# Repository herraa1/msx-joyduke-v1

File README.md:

# Microsoft Xbox Original controller adapter for MSX (msx-joyduke) v1

Connect [Microsoft Xbox Original controllers](https://en.wikipedia.org/wiki/Xbox_controller) to [MSX computers](https://www.msx.org/wiki/).

> [!NOTE]
>
> No build instructions are yet provided, but if you are brave enough go for the [recommended build](#recommended-build).
>

## Introduction

The msx-joyduke v1 is an adapter that allows connecting Microsoft Xbox Original controllers to [MSX general purpose I/O ports](https://www.msx.org/wiki/General_Purpose_port).

The main features of the msx-joyduke v1 adapter are:
* made of widely available electronic components
* behaves as a cord extension between the MSX computer and the Microsoft Xbox Original controller
* uses a female standard DE9 connector on the adapter's MSX joystick side
* uses a Xbox Controller socket on the adapter's Microsoft Xbox Original controller side
* formally requires an external USB power supply as the adapter draws slightly more current than a MSX general purpose I/O interface can officially provide
* optionally, can be powered using a MSX general purpose I/O interface without an external power supply if your MSX can safely supply enough current
* power consumption of ~20mA for the adapter itself, between ~55mA and ~85mA depending on the Xbox controller connected
* serial debug provides information about the operation of the adapter

## [Hardware](hardware/kicad/)

The msx-joyduke v1 adapter uses an [Atmega328p](https://en.wikipedia.org/wiki/ATmega328) and a [MAX3421](https://www.analog.com/media/en/technical-documentation/data-sheets/max3421e.pdf) to convert the [Microsoft Xbox Original controller USB signalling](https://xboxdevwiki.net/Xbox_Input_Devices#USB_Adapters) to the [MSX joystick standard signalling](https://www.msx.org/wiki/Joystick_control).

A two-sided printed circuit board (PCB) is used to put together all components:
* An Atmega328p as the main MCU working at +3.3V and clocked at 8MHz
* A MAX3421 USB Host Controller with SPI interface
* A TPS2051C 500mA current limited switch for the host controller USB port
* An AMS1117-3.3 regulator to convert the 5V from the joystick or the mini USB port to the 3.3V used by the Atmega328p and the MAX3421 chips
* Two 74LS03 quad 2-input NAND gates with open collectors to completely mimic the standard MSX joystick behavior
* A PTC fuse to minimize damage to the MSX computer in case something goes wrong with the board
* Several additional required components (crystals/resonators, diodes, leds, resistors, ceramic capacitors and alumionium capacitors)
* A 9pin PH2.0 connector is used to connect the MSX cable extension
* A 5pin PH2.0 connector is used to connect the Xbox cable extension
* A 2.54 pitch debug header is added for serial debug and programming
* An ICSP header is provided for burning a bootloader or to flash the chip using a hardware programmer

Connection to the MSX general purpose I/O port is implemented using a DE9 joystick extension cable with a female DE9 connector on one side and a loose end on the other side.
The MSX joystick extension cable loose end is wired according to the following pinout mapping.

|  |
|:--|
| MSX joystick connector pinout, from controller plug side |

| MSX side pin | Cable color (may vary) | Signal |
| ------------ | ---------------------- | ------ |
| 5            | Brown                  | +5v    |
| 4            | Orange                 | RIGHT  |
| 3            | Grey                   | LEFT   |
| 2            | Black                  | DOWN   |
| 1            | Red                    | UP     |
| 6            | Green                  | TRIGA  |
| 7            | White                  | TRIGB  |
| 8            | Blue                   | OUT    |
| 9            | Yellow                 | GND    |

The msx-joyduke-v1 is fully compatible with MSX joysticks and honors the pin8 (OUT) signal.

Connection to the Microsoft Xbox Original controller is done via a PC USB for Microsoft Xbox Original controller converter adapter cable with a male socket (the ones present on the Xbox console itself).

|  |
|:--|
| PC USB for Microsoft Xbox Original controller adapter cable |

The cable is severed to get rid of the USB side (which can be used for other projects) exposing the USB wiring.

|  |
|:--|
| Microsoft Xbox Original connector pinout, from Microsoft Xbox Original controller side |

| Cable color official | Signal       | Comment                                                                   |
| ---------------------| ------------ | ------------------------------------------------------------------------- |
| Green                | D+           | USB Data +                                                                |
| White                | D-           | USB Data -                                                                |
| Yellow               | VSync        | (not used)                                                                |
| Black                | GND          | ground                                                                    |
| Red                  | +5V          | +5V power                                                                 |

The Microsoft Xbox Original controller uses 5V for power and logic.

### Recommended Build

Please, use [msx-joyduke-v1 Build2](#build2) for making new boards.

### [Build2](hardware/kicad/msx-joyduke-v1-build2)

[Bill Of Materials (BoM)](https://html-preview.github.io/?url=https://raw.githubusercontent.com/herraa1/msx-joyduke-v1/main/hardware/kicad/msx-joyduke-v1-build2/bom/ibom.html)

This is the first publicly released build of the msx-joyduke adapter.

## [Firmware](firmware/msx-joyduke-v1/)

The msx-joyduke v1 adapter firmware uses the [USB Host Shield 2.0 library](https://github.com/felis/USB_Host_Shield_2.0) to read the Microsoft Xbox Original controller status.

While developing the firmware, I noticed that some Xbox Original controllers were not working as expected. After a bit of troubleshooting the root cause was found and a [modification](https://github.com/felis/USB_Host_Shield_2.0/commit/b92fa02546dddd2278cd411e5d0e2d2ff614c8d8) to the library has been submitted and merged to fix the problem.

The following elements are used as inputs:
* digital pad (D-Pad), as direction arrows
* left and right analog pad as direction arrows
* A button, as Trigger 1
* B button, as Trigger 2

Those elements' status are processed by the msx-joyduke firmware and transformed into MSX general purpose I/O port's signals on the fly.

## [Enclosure](enclosure/)

### Acrylic

A simple acrylic enclosure design for the project is provided to protect the electronic components and provide strain relief for the extension cords.

The enclosure uses a 3mm acrylic sheet.

## Powering the msx-joyduke adapter

The msx-joyduke adapter uses under ~20mA when operating without a controller connected, but the power consumption can rise to ~85mA when an Xbox controller is connected.

On the other hand, a single MSX general purpose I/O interface is capable of delivering up to 50mA according to the MSX standard [^1].

That means that we are slightly over the max current specification for the MSX general purpose I/O interface.

Thus, the safest way to power the msx-joyduke adapter is by powering it via the USB mini connector of the board using an external 5V USB power supply. The board automatically powers up when using the USB mini connector without enabling any switch.

Nevertheless, even if the MSX especification puts such a low limit on the current that can be drawn from a general purpose I/O interface, real MSX hardware usually can safely deliver enough current for the msx-joyduke adapter to work correctly without harming our beloved classic computers.

Taking that into account, the msx-joyduke adapter has been enabled to be optionally powered by the a MSX general purpose I/O interface port.

To enable powering the msx-joyduke adapter from the _MSX Joystick Port_, the switch SW1 _JOYPWR_ must be first turned on by sliding the switch handle to the left.

> [!NOTE]
> A [1N5819 SMD Schottky diode](https://www.diodes.com/assets/Datasheets/1N5819HW.pdf) D4 is used to avoid leaking current from the msx-joyduke adapter to the MSX in case the msx-joyduke adapter is powered by USB while the _JOYPWR_ switch is ON.
> Another [1N5819 SMD Schottky diode](https://www.diodes.com/assets/Datasheets/1N5819HW.pdf) D3 prevents backpowering the USB side from the MSX side.
> And a Positive Temperature Coeficient (PTC) resettable fuse F1 of 50mA protects the MSX general purpose I/O interface port from excess of current in case something goes horribly wrong on the msx-joyduke adapter side.

To power the msx-joyduke adapter using a MSX general purpose I/O interface we must first understand how the PTC protections on the msx-joyduke adapter are implemented.

The selected PTC is rated for 50mA which is the so called Hold Current (the maximum current that can flow in normal operation). There is also the Trip Current (the minimum current necessary for the PTC to move to high-resistance state) which for the selected PTCs is around 100mA. Those thresholds are dependent on temperature and voltage. And to make things more undeterministic, the behavior of the PTC when current is between those thresholds is undefined (it may trip or not).

In normal operation and for a room temperature of around 25 degrees Celsius, the selected PTCs in practice never trip below 75mA.

> [!NOTE]
> Depending on the exact PTCs installed, the trip current may be slightly different and the adapter may trip at a different point. Unless you buy the PTCs from a reliable source, it is very difficult to know the exact PTC specifications. 
>
> Remember that the PTCs are provided as a safeguard in case something goes really wrong on the adapter, not to act as an exact current limiter to strictly comply with the 50mA per-port MSX specification.

A jumper JP1 can be used to bypass the PTC protections for the _MSX Joystick Port_.

> [!WARNING]
> Bypassing the PTC protection may damage your MSX computer.
> Do not bypass the PTC protections unless you known what you are doing.

By closing JP1 and **if our MSX computer can safely provide more than 85mA on a single MSX general purpose I/O interface**, we can connect the _MSX Joystick Port_ to the MSX computer and turn on the SW1 _JOYPWR_ switch to power the msx-joyduke adapter using a single joystick port.

In summary, we can use the following options to power the msx-joyduke adapter (from safest to less safe):
* via the board USB mini conector
  * turn off the SW1 _JOYPWR_ switch
  * connect a 5V USB power supply to the board USB mini connector
* via one of the MSX general purpose I/O interface, if your MSX can safely provide more than 85mA on each MSX general purpose I/O interface
  * close jumper JP1
  * turn on the SW1 _JOYPWR_ switch
  * connect the _MSX Joystick Port_ to a MSX general purpose I/O interface

## Switches and Buttons

| **Switch** | **State**      | **Description**                                                          |
|------------|----------------|--------------------------------------------------------------------------|
| _JOYPWR_   | Off            | power from MSX computer via a joystick port is off (except logic gates)  |
| _JOYPWR_   | On             | board electronics get power from MSX computer via a joystick port        |

> [!NOTE]
> If you plug a +5V USB power supply to the USB mini connector, the adapter will turn on unconditionally irrespective of the _JOYPWR_ switch position.
>

| **Button**   | **Description**                                                                             |
|--------------|---------------------------------------------------------------------------------------------|
| RESET        | restart the firmware                                                                        |

## LED indicators

| **LED**   | **State**      | **Indication** |
|-----------|----------------|---------------|
| _POWER_   | Off            | board is not receiving 3V3 power |
| _POWER_   | Solid Red      | board is receiving 3V3 power     |
| _JoyPort_ | Off            | no Xbox controller connected or recognized |
| _JoyPort_ | Solid Green    | Xbox controller connected and ready to use |
| _Fault_   | Off            | no power fault detected |
| _Fault_   | Solid Yellow   | excess of current detected on the Xbox connector |

## Compatibility Tests

| **Controller**                        | **Compatible** |
|---------------------------------------|----------------|
| 045e:0202 Microsoft X-Box pad v1 (US) | YES            |
| 045e:0289 Microsoft X-Box pad v2 (US) | YES            |

Other Xbox controllers may work but have not been tested.

## References

MSX general purpose I/O port
* https://www.msx.org/wiki/General_Purpose_port

Xbox controller pinout and protocol
* https://chris-donnelly.github.io/xboxpad.html

Atmega328p pinout
- https://camo.githubusercontent.com/18796d8b7673e3b6c14b6bdfb61d86b58c6f0d670398973abd4207afce960277/68747470733a2f2f692e696d6775722e636f6d2f6e6177657145362e6a7067

USB Host Shield 2.0 Library
* https://github.com/felis/USB_Host_Shield_2.0

[^1]: https://www.msx.org/wiki/General_Purpose_port

## Image Sources

* https://www.oshwa.org/open-source-hardware-logo/
* https://en.wikipedia.org/wiki/File:Numbered_DE9_Diagram.svg

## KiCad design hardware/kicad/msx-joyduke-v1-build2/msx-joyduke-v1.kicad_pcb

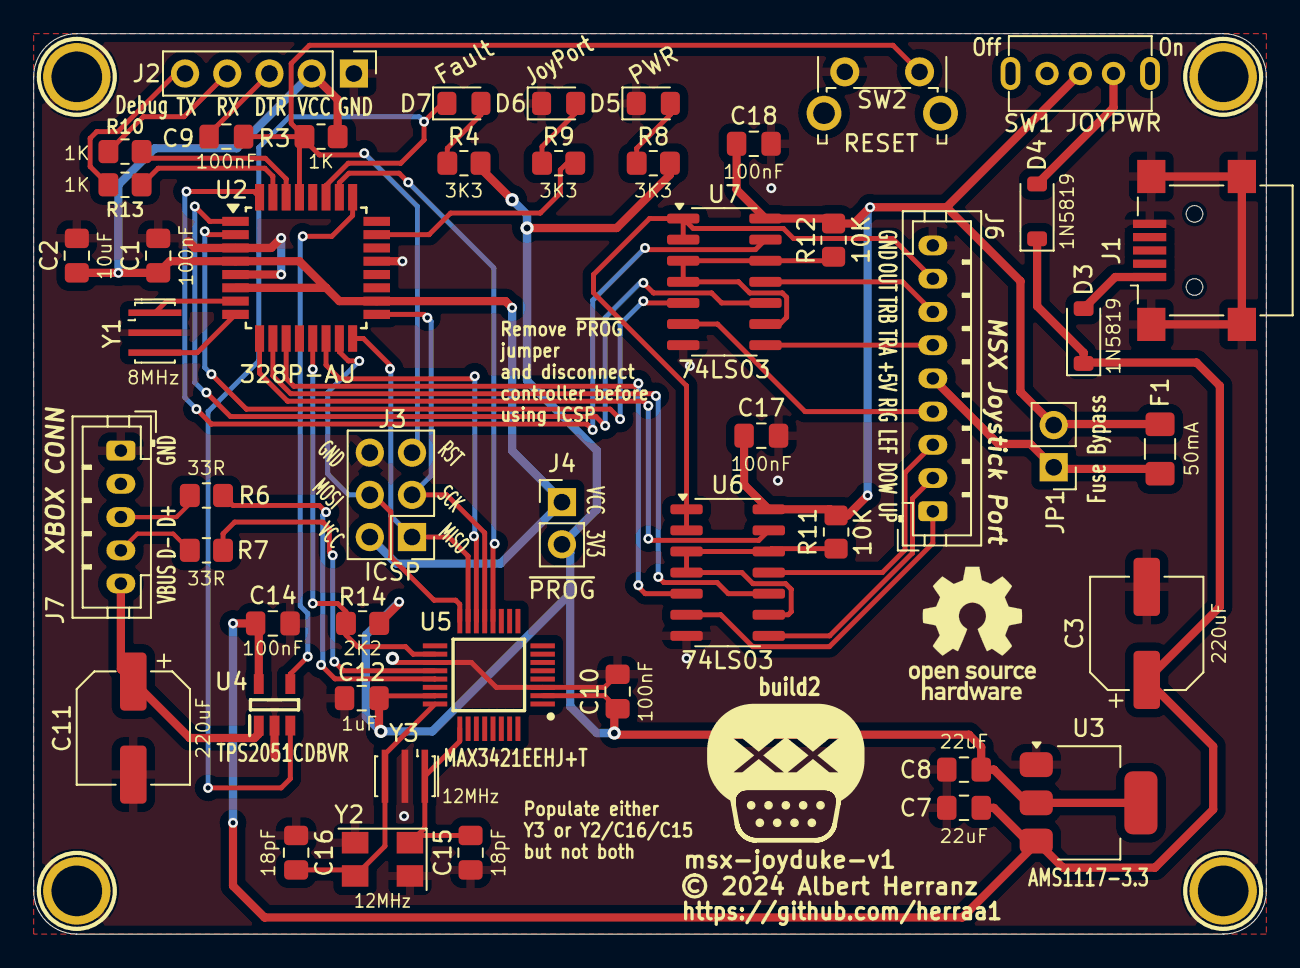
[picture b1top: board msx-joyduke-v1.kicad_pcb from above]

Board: 2 copper layers, 74.2 x 54.2 mm, 54 parts (0 on the bottom side), 50 nets.

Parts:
C1, C9, C10, C14, C17, C18: 100nF; C_0805_2012Metric_Pad1.18x1.45mm_HandSolder
C2: 10uF; C_0805_2012Metric_Pad1.18x1.45mm_HandSolder
C3, C11: 220uF; CP_Elec_6.3x5.4
C7, C8: 22uF; C_0805_2012Metric_Pad1.18x1.45mm_HandSolder
C12: 1uF; C_0805_2012Metric_Pad1.18x1.45mm_HandSolder
C15, C16: 18pF; C_0805_2012Metric_Pad1.18x1.45mm_HandSolder
D3, D4: 1N5819; D_SOD-123
D5: PWR; LED_0805_2012Metric_Pad1.15x1.40mm_HandSolder
D6: JoyPort; LED_0805_2012Metric_Pad1.15x1.40mm_HandSolder
D7: Fault; LED_0805_2012Metric_Pad1.15x1.40mm_HandSolder
F1: 50mA; Fuse_1206_3216Metric_Pad1.42x1.75mm_HandSolder
HOLE1, HOLE2, HOLE3, HOLE4: HOLE; Hole_3mm
J1: USB_B_Mini; USB_Mini-B_Lumberg_2486_01_Horizontal
J2: Debug; PinHeader_1x05_P2.54mm_Vertical
J3: ICSP; PinHeader_2x03_P2.54mm_Vertical
J4: ~{PROG}; PinHeader_1x02_P2.54mm_Vertical
J6: MSX Joystick Port; JST_PH_B9B-PH-K_1x09_P2.00mm_Vertical
J7: XBOX CONN; JST_PH_B5B-PH-K_1x05_P2.00mm_Vertical
JP1: Fuse Bypass; PinHeader_1x02_P2.54mm_Vertical
R3, R10, R13: 1K; R_0805_2012Metric_Pad1.20x1.40mm_HandSolder
R4, R8, R9: 3K3; R_0805_2012Metric_Pad1.20x1.40mm_HandSolder
R6, R7: 33R; R_0805_2012Metric_Pad1.20x1.40mm_HandSolder
R11, R12: 10K; R_0805_2012Metric_Pad1.20x1.40mm_HandSolder
R14: 2K2; R_0805_2012Metric_Pad1.20x1.40mm_HandSolder
SW1: JOYPWR; SW_SK-12D07G6-1P2T-6mm
SW2: RESET; SW_Tactile_SPST_Angled_PTS645Vx39-2LFS
SYM1: Logo_Open_Hardware_Large; OSHW-Logo_7.5x8mm_SilkScreen
U2: 328P-AU; TQFP-32_7x7mm_P0.8mm
U3: AMS1117-3.3; SOT-223-3_TabPin2
U4: TPS2051CDBVR; SOT95P280X145-5N
U5: MAX3421EEHJ+T; QFP50P700X700X120-32N
U6, U7: 74LS03; SOIC-14_3.9x8.7mm_P1.27mm
Y1: 8MHz; Resonator_SMD_Murata_CSTxExxV-3Pin_3.0x1.1mm_HandSoldering
Y2: 12MHz; Crystal_SMD_5032-4Pin_5.0x3.2mm
Y3: 12MHz; Resonator_SMD_Murata_CSTxExxV-3Pin_3.0x1.1mm_HandSoldering

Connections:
+3V3_REG: C8.1, C10.1, C12.1, J4.2, R4.2, R8.2, R14.1, U3.2 (VO), U5.2 (VL), U5.23 (VCC)
+5V_FILT: C3.1, C7.1, C14.1, D3.1 (K), D4.1 (K), U3.3 (VI), U4.5 (IN)
/+3V3_LED: D5.2 (A), R8.1
/D0/RX: R10.1, U2.30 (PD0)
/D1/TX: R13.1, U2.31 (PD1)
/DTR: C9.2, J2.3
/D_N: J7.4, R7.2
/D_P: J7.3, R6.2
/GPIO_J1_DOWN: U2.10 (PD6), U6.10
/GPIO_J1_LEFT: U2.9 (PD5), U6.13
/GPIO_J1_RIGHT: U2.2 (PD4), U7.5
/GPIO_J1_TRIGA: U2.1 (PD3), U7.10
/GPIO_J1_TRIGB: U2.32 (PD2), U7.13
/GPIO_J1_UP: U2.11 (PD7), U6.5
/J1_DOWN: J6.2, U6.8
/J1_LEFT: J6.3, U6.11
/J1_OUT: J6.8, U6.1, U6.2, U7.1, U7.2
/J1_RIGHT: J6.4, U7.6
/J1_TRIGA: J6.6, U7.8
/J1_TRIGB: J6.7, U7.11
/J1_UP: J6.1, U6.6
/JOY_EXT_5V: D4.2 (A), SW1.1 (A)
/MISO: J3.1, U2.16 (PB4), U5.15 (MISO)
/MOSI: J3.4, U2.15 (PB3), U5.16 (MOSI)
/RESET: C9.1, J3.5, R3.2, SW2.2, U2.29 (~RESET/PC6)
/SCK: J3.3, U2.17 (PB5), U5.13 (SCLK)
/SS: U2.14 (PB2), U5.14 (~SS)
/USB_EXT_5V: D3.2 (A), J1.1 (VBUS)
/~J1_OUT_1: R11.2, U6.3, U6.4, U6.9, U6.12
/~J1_OUT_2: R12.2, U7.3, U7.4, U7.9, U7.12
FAULT: D7.1 (K), U2.27 (PC4), U4.3 (~FLT)
GND: C1.2, C2.2, C3.2, C7.2, C8.2, C10.2, C11.2, C12.2, C14.2, C15.1, C16.1, C17.2, C18.2, D5.1 (K), D6.1 (K), HOLE1.1, HOLE2.1, HOLE3.1, HOLE4.1, J1.5 (GND), J1.6 (Shield), J2.1, J3.6, J6.9, J7.1, SW2.1, U2.3 (GND), U2.5 (GND), U2.21 (GND), U3.1 (GND), U4.2 (GND), U5.3 (GND_1), U5.19 (GND_2), U6.7 (GND), U7.7 (GND), Y1.2, Y2.2, Y2.4, Y3.2
INT1: R14.2, U2.13 (PB1), U5.18 (INT)
J1_PWR: F1.1, J6.5, JP1.1 (A)
JOY_5V: C17.1, C18.1, F1.2, JP1.2 (B), R11.1, R12.1, SW1.2 (B), U6.14 (VCC), U7.14 (VCC)
LED_J1: R9.2, U2.23 (PC0)
MCU_VCC: C1.1, C2.1, J2.2, J3.2, J4.1, R3.1, U2.4 (VCC), U2.6 (VCC), U2.18 (AVCC)
unnamed: D6.2 (A), R9.1
unnamed: D7.2 (A), R4.1
unnamed: U2.7 (XTAL1/PB6), Y1.1
unnamed: U2.8 (XTAL2/PB7), Y1.3
unnamed: R6.1, U5.21 (D+)
unnamed: R7.1, U5.20 (D-)
UART_RX: J2.4, R10.2
UART_TX: J2.5, R13.2
UHC_EN: U2.26 (PC3), U5.12 (~RES)
VBUS: C11.1, J7.5, U4.1 (OUT)
VUSB_EN: U2.25 (PC2), U4.4 (EN/~EN)
XTAL_0: C15.2, U5.25 (XO), Y2.1, Y3.1
XTAL_1: C16.2, U5.24 (XI), Y2.3, Y3.3

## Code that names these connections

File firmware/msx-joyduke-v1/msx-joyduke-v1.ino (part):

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XBOXOLD Xbox(&Usb);

const byte PIN_HAVECONTROLLER = A0;
const byte PIN_UHC_EN = A3;
const byte PIN_VUSB_EN = A2;

/*
 * Atmega328p pins for MSX signals.
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#define DDR_MSX_JOYSTICK DDRD

/* MSX general purpose signals as mapped to Atmega328p PORTD bits */
const int PORT_MSX_JOYSTICK_UP = 7;       /* PD7, MSX joystick pin1 */
const int PORT_MSX_JOYSTICK_DOWN = 6;     /* PD6, MSX joystick pin2 */
const int PORT_MSX_JOYSTICK_LEFT = 5;     /* PD5, MSX joystick pin3 */
const int PORT_MSX_JOYSTICK_RIGHT = 4;    /* PD4, MSX joystick pin4 */
const int PORT_MSX_JOYSTICK_TRIGGER1 = 3; /* PD3, MSX joystick pin6 */
const int PORT_MSX_JOYSTICK_TRIGGER2 = 2; /* PD2, MSX joystick pin7 */

volatile uint8_t curr_msx_joystick_signals = 0x00;

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  int16_t axis_threshold;

  pinMode(PIN_HAVECONTROLLER, OUTPUT);
  pinMode(PIN_UHC_EN, OUTPUT);
  pinMode(PIN_VUSB_EN, OUTPUT);

  __update_msx_signals(curr_msx_joystick_signals);

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  Serial.print("axis_threshold_min: ");
  Serial.println(axis_threshold_min);

  digitalWrite(PIN_VUSB_EN, HIGH);
  delay(150);
  digitalWrite(PIN_UHC_EN, HIGH);

  if (Usb.Init() == -1) {
    Serial.println(F("OSC did not start, halting!"));
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
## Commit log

2024-07-17 readme: redaction fixes, add compatibility table
2024-07-17 readme: enhance redaction and add tps2051c current limited switch info
2024-08-18 readme: add comment about USB Host Shield 2.0 library fix
2024-12-25 readme: add microprocessor clock
2024-12-25 readme: no build instructions yet

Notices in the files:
firmware/msx-joyduke-v1/msx-joyduke-v1.ino:
Copyright (C) 2024 Albert Herranz
This code is released under GPL V2.0
Valid-License-Identifier: GPL-2.0-only
SPDX-URL: https://spdx.org/licenses/GPL-2.0-only.html
hardware/kicad/msx-joyduke-v1-build2/msx-joyduke-v1.kicad_pcb:
© 2024 Albert Herranz
